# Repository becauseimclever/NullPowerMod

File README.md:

# NullPowerMod
Drop in replacement for the Null 2 power board.

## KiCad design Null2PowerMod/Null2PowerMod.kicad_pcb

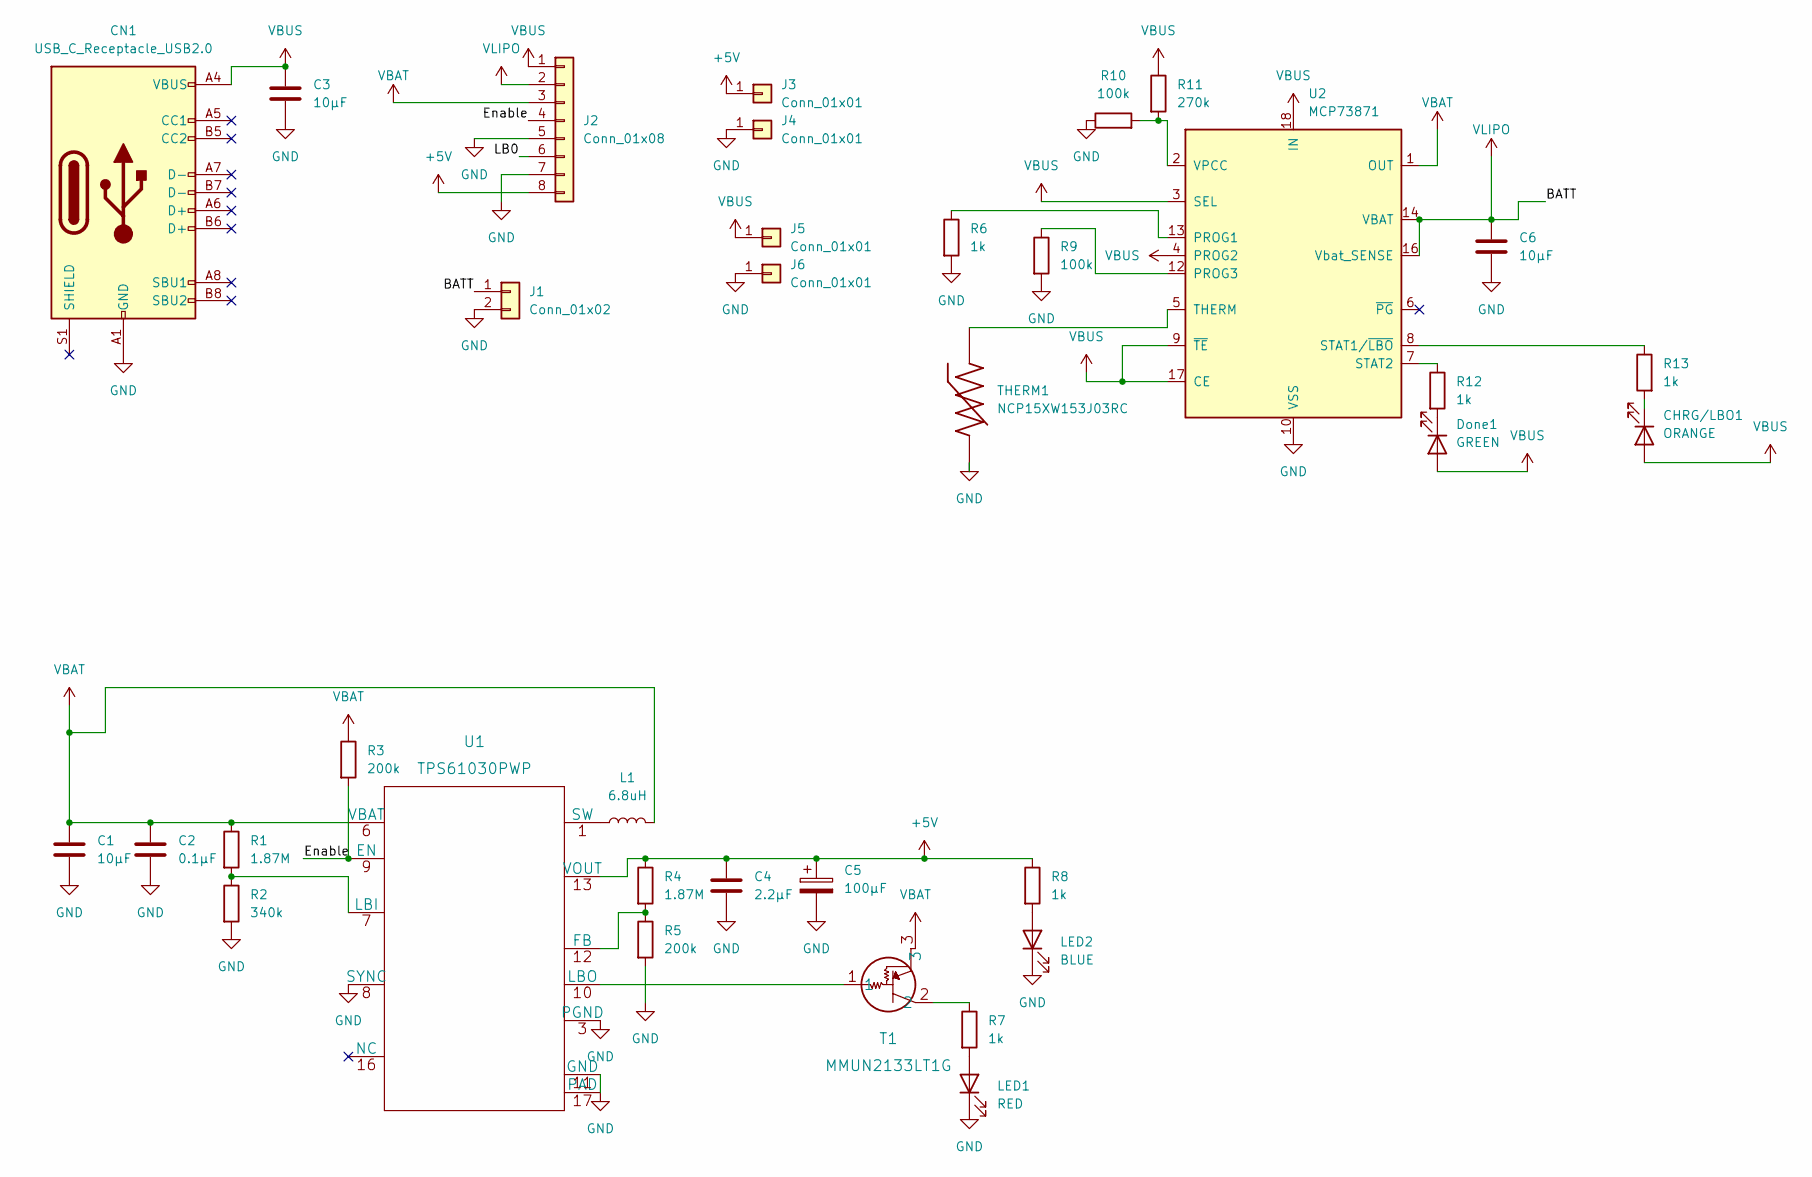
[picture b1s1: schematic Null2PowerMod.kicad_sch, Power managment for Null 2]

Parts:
C1, C3, C6: 10μF; C_0201_0603Metric
C2: 0.1μF; C_0201_0603Metric
C4: 2.2μF; C_0201_0603Metric
C5: 100μF; C_0201_0603Metric
CHRG/LBO1: ORANGE; LED_0201_0603Metric
CN1: USB_C_Receptacle_USB2.0; USB_C_Receptacle_GCT_USB4085
Done1: GREEN; LED_0201_0603Metric
J1: Conn_01x02; JST_EH_S2B-EH_1x02_P2.50mm_Horizontal
J2: Conn_01x08; PinHeader_1x08_P1.00mm_Vertical
J3, J4, J5, J6: Conn_01x01; PinHeader_1x01_P2.54mm_Vertical
L1: 6.8uH; VLC5045T-330M
LED1: RED; LED_0201_0603Metric
LED2: BLUE; C_0201_0603Metric
R1, R4: 1.87M; R_0201_0603Metric
R2: 340k; R_0201_0603Metric
R3, R5: 200k; R_0201_0603Metric
R6, R7, R12, R13: 1k; R_0201_0603Metric
R8: 1k; C_0201_0603Metric
R9, R10: 100k; R_0201_0603Metric
R11: 270k; R_0201_0603Metric
T1: MMUN2133LT1G
THERM1: NCP15XW153J03RC; THRMC1005X55N
U1: TPS61030PWP
U2: MCP73871; QFN-20-1EP_4x4mm_P0.5mm_EP2.5x2.5mm

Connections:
+5V: C4.1, C5.1, J2.8, J3.1, R4.1, R8.1, U1.13 (VOUT), U1.14 (VOUT), U1.15 (VOUT)
/Enable: J2.4, R3.2, U1.9 (EN)
/LB0: J2.6
GND: C1.2, C2.2, C3.2, C4.2, C5.2, C6.2, CN1.A1 (GND), CN1.A12 (GND), CN1.B1 (GND), CN1.B12 (GND), J1.2, J2.5, J2.7, J4.1, J6.1, LED1.1 (K), LED2.1 (K), R2.2, R5.2, R6.2, R9.2, R10.1, THERM1.2, U1.3 (PGND), U1.4 (PGND), U1.5 (PGND), U1.8 (SYNC), U1.11 (GND), U1.17 (PAD), U2.10 (VSS), U2.11 (VSS), U2.21 (VSS)
unnamed: CHRG/LBO1.1 (K), R13.2
unnamed: Done1.1 (K), R12.2
unnamed: LED1.2 (A), R7.2
unnamed: LED2.2 (A), R8.2
unnamed: R1.2, R2.1, U1.7 (LBI)
unnamed: R4.2, R5.1, U1.12 (FB)
unnamed: R6.1, U2.13 (PROG1)
unnamed: R7.1, T1.2
unnamed: R9.1, U2.12 (PROG3)
unnamed: R10.2, R11.2, U2.2 (VPCC)
unnamed: R12.1, U2.7 (STAT2)
unnamed: R13.1, U2.8 (STAT1/~LBO)
unnamed: T1.1, U1.10 (LBO)
unnamed: THERM1.1, U2.5 (THERM)
SW: L1.1, U1.1 (SW), U1.2 (SW)
VBUS: C3.1, CHRG/LBO1.2 (A), CN1.A4 (VBUS), CN1.A9 (VBUS), CN1.B4 (VBUS), CN1.B9 (VBUS), Done1.2 (A), J2.1, J5.1, R11.1, U2.3 (SEL), U2.4 (PROG2), U2.9 (~TE), U2.17 (CE), U2.18 (IN), U2.19 (IN)
VLIPO: C6.1, J1.1, J2.2, U2.14 (VBAT), U2.15 (VBAT), U2.16 (Vbat_SENSE)

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
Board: 2 copper layers, 35 parts (0 on the bottom side), 22 nets, no tracks yet.

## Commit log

2022-03-16 JSONAPI maybe?
2022-03-17 Deciding on TPS61030PWP
2022-03-20 expirementing with new tch
2022-03-20 Fully routed
2022-03-20 Feedback changes
2022-03-20 implementing feedback
2022-03-21 sync
2022-03-21 fixing power symbols
2022-03-21 wtf happened to the schematic?
2022-03-21 updating schematic, re-starting the pcb completly
2022-03-26 Major part overhaul
2022-03-26 Refreshed ideas for next milestone
2022-03-27 Redesigning pcb
2022-03-28 Major revision
2022-04-19 Trying out an autorouter
2022-04-19 Reset and try again

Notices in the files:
parts and their libraries:
Copyright 2021 Accelerated Designs. All rights reserved.
